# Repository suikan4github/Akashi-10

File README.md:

# Akashi-10
Test board of the EL-210 calculator
## Description
This board is developed to test the functionality of the EL-210 Calculator controller. The [EL-210](https://vintage-technology.club/pages/calculators/sharp/sharpel210.htm) was released from SHARP Corporation at 1980. 

This board tests its internal 9 digits VFD and 9x3 matrix keyboard. All signals and power from internal AA*2 batteries are taken out by 40pin headers. 
## Pin assignment
The ping assignment of the 40pin headers are as followings : 

 Pin | Symbol | Pin | Symbol 
 ----|--------|-----|-------
 1   | H1     | 2   | H2
 3   | a      | 4   | 
 5   | D8     | 6   | KR0
 7   | g      | 8   | KR1
 9   | D7     | 10  | KR2
 11  | f      | 12  | KC0
 13  | D6     | 14  | KC1
 15  | e      | 16  | KC2
 17  | D5     | 18  | KC3
 19  | D4     | 20  | KC4
 21  | d      | 22  | KC5
 23  | D3     | 24  | KC6
 25  | dp     | 26  | KC7
 27  | D2     | 28  | KC8
 29  | c      | 20  | 
 31  | D1     | 32  | 
 33  | b      | 34  | 
 35  | D0     | 36  | 
 37  | H2     | 38  | 
 39  | H1     | 20  | 

Where odd and even pins are signals of the VFD and the key matrix. 
- H1, H2 : Heater.
- a .. f and dp : Segments ( Anode ).
- D0 .. D8 : Digits ( grid ). 
- R1 .. R3 : Row 1 .. 3 of the key matrix.
- C0 .. C8 : Column 0 .. 8 of the key matrix.

## Gallery
This is photo of the version 1.0.2.

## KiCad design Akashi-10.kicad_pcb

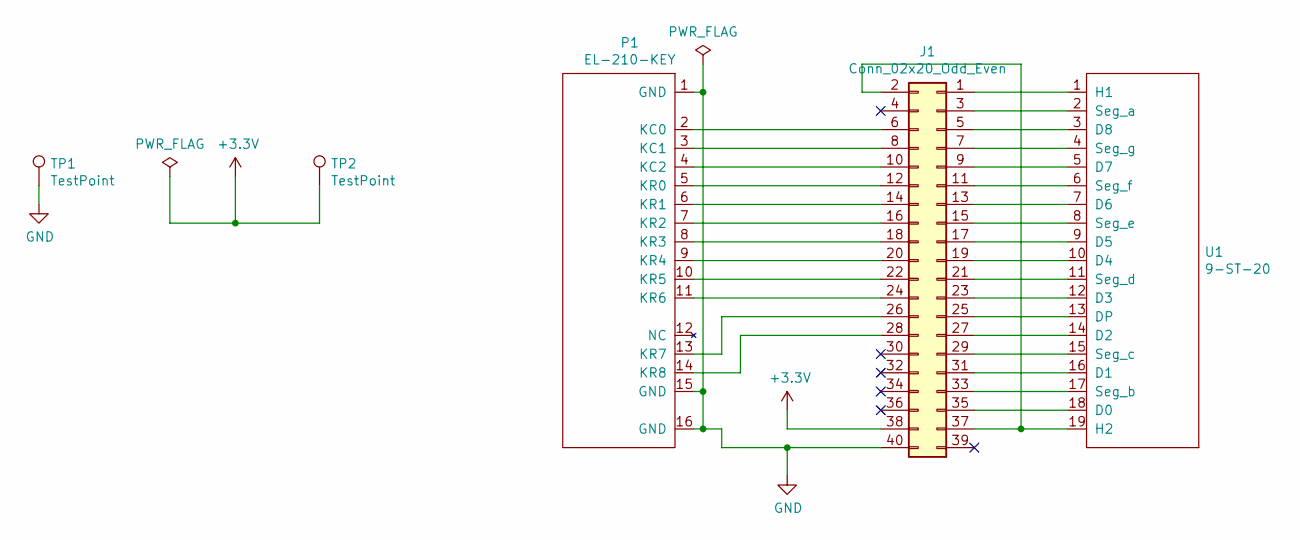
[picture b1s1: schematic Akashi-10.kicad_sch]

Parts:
J1: Conn_02x20_Odd_Even; PinHeader_2x20_P2.54mm_Vertical
P1: EL-210-KEY
TP1, TP2: TestPoint; TestPoint_Loop_D2.60mm_Drill0.9mm_Beaded
U1: 9-ST-20

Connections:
+3V3: J1.38, TP2.1
GND: J1.40, P1.1 (GND), P1.15 (GND), P1.16 (GND), TP1.1
unnamed: J1.1, U1.1 (H1)
unnamed: J1.2, J1.37, U1.19 (H2)
unnamed: J1.3, U1.2 (Seg_a)
unnamed: J1.5, U1.3 (D8)
unnamed: J1.6, P1.2 (KC0)
unnamed: J1.7, U1.4 (Seg_g)
unnamed: J1.8, P1.3 (KC1)
unnamed: J1.9, U1.5 (D7)
unnamed: J1.10, P1.4 (KC2)
unnamed: J1.11, U1.6 (Seg_f)
unnamed: J1.12, P1.5 (KR0)
unnamed: J1.13, U1.7 (D6)
unnamed: J1.14, P1.6 (KR1)
unnamed: J1.15, U1.8 (Seg_e)
unnamed: J1.16, P1.7 (KR2)
unnamed: J1.17, U1.9 (D5)
unnamed: J1.18, P1.8 (KR3)
unnamed: J1.19, U1.10 (D4)
unnamed: J1.20, P1.9 (KR4)
unnamed: J1.21, U1.11 (Seg_d)
unnamed: J1.22, P1.10 (KR5)
unnamed: J1.23, U1.12 (D3)
unnamed: J1.24, P1.11 (KR6)
unnamed: J1.25, U1.13 (DP)
unnamed: J1.26, P1.13 (KR7)
unnamed: J1.27, U1.14 (D2)
unnamed: J1.28, P1.14 (KR8)
unnamed: J1.29, U1.15 (Seg_c)
unnamed: J1.31, U1.16 (D1)
unnamed: J1.33, U1.17 (Seg_b)
unnamed: J1.35, U1.18 (D0)

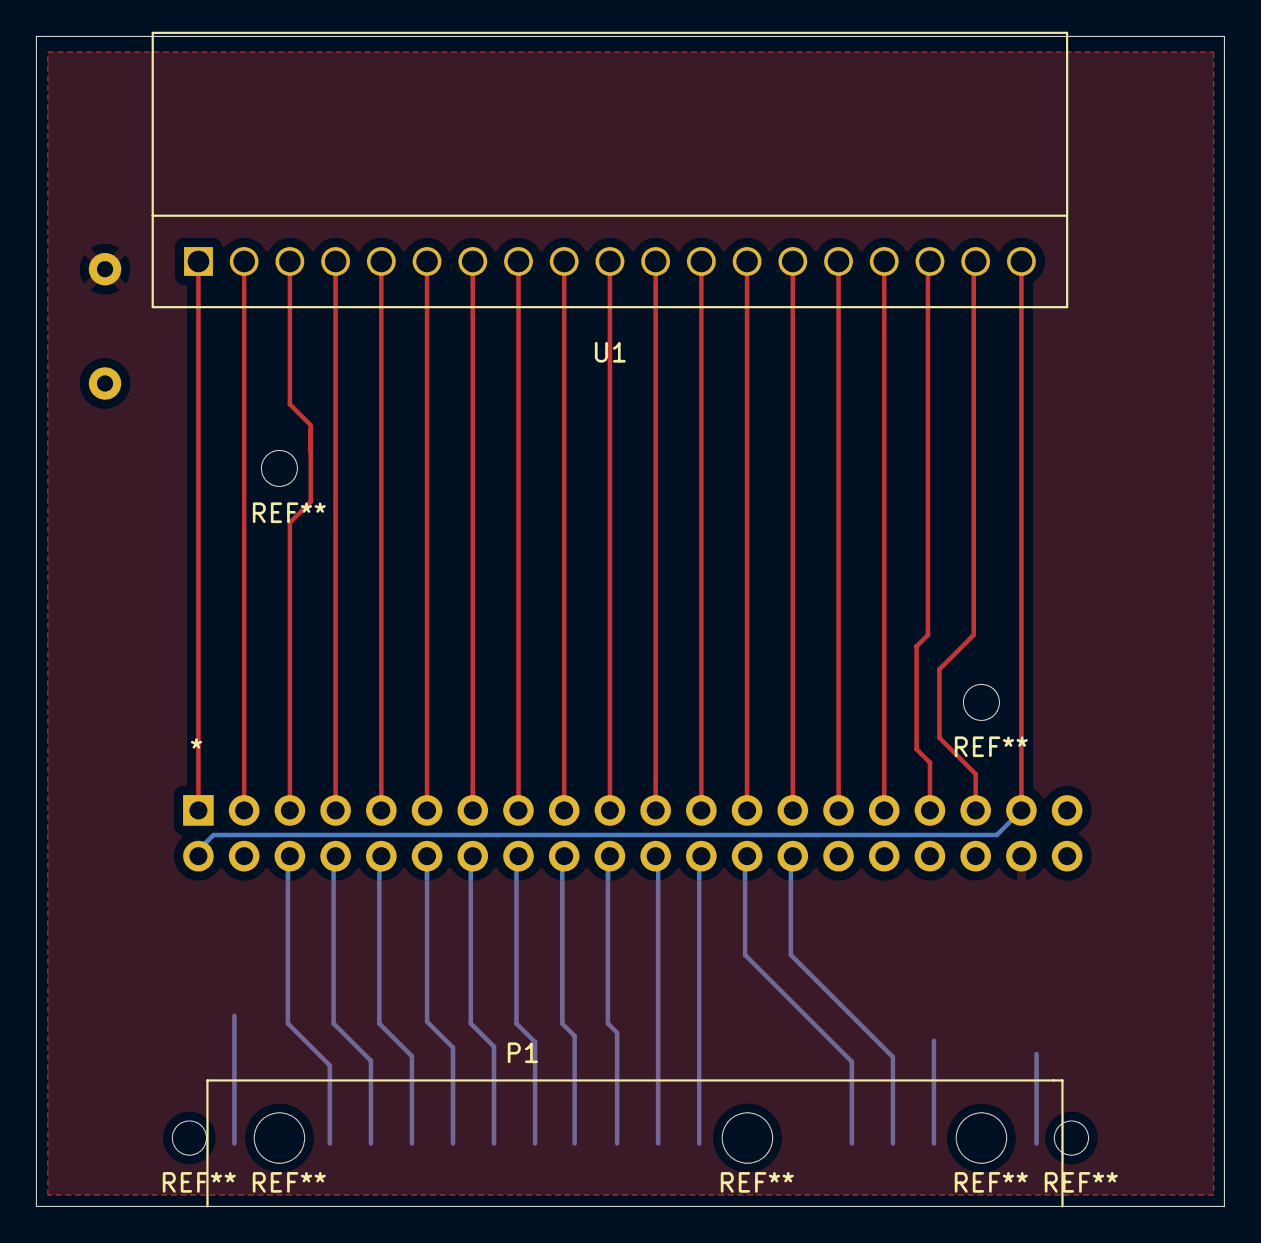
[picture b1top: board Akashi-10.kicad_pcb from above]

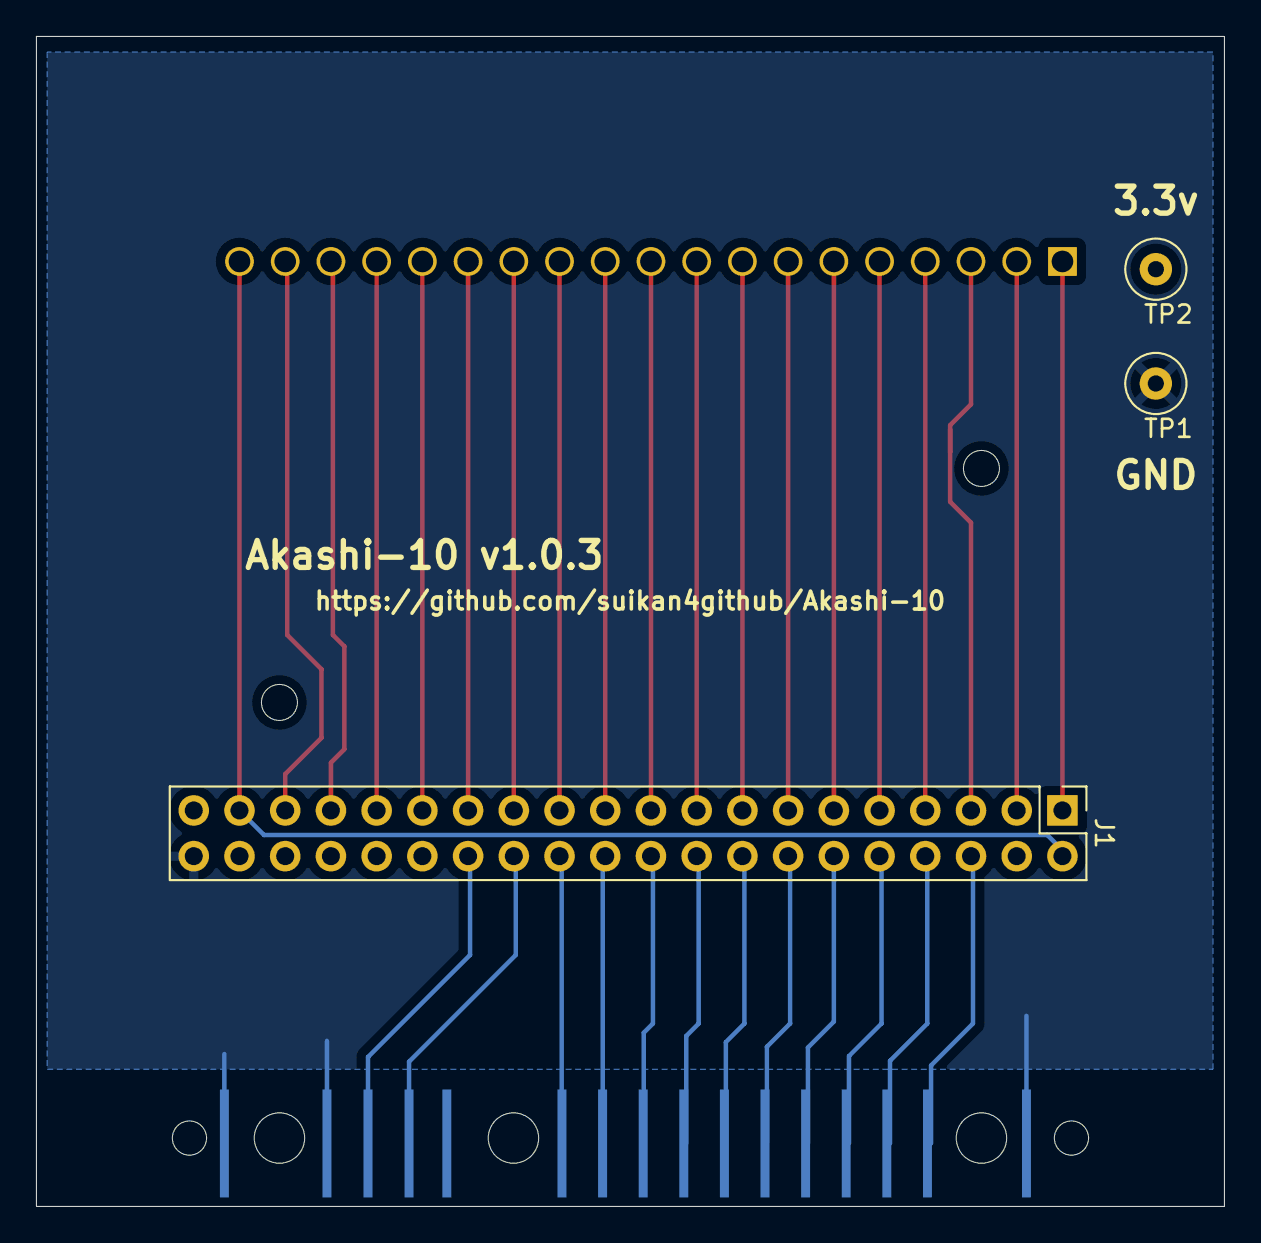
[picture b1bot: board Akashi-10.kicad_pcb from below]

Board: 2 copper layers, 66.0 x 65.0 mm, 5 parts (3 on the bottom side), 33 nets.

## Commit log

2022-06-04 Add 9-ST-20 symbol and footprint
2022-06-05 Add EL-210-key
2022-06-09 place initial layout
2022-06-12 Add holes
2022-06-12 All routed
    No DRC error
2022-06-12 Add version number to Silk
2022-06-12 Sent v1.0.0 to FusionPCB
2022-06-25 P1 pattern fixed.
    Hole size changed. GND/3.3V position changed.
2022-07-10 Add lost holes.
2022-07-11 Lock hole footprints on PCB.
    To prevent delete them during the updating PCB from schematics.
2022-08-11 Apply library modification to board.
2022-10-11 v1.0.2
2023-01-11 Fixed name of the KEY matrix sisgnal.
    The Row signal order was up-side-down. Fixed.
    The Col signal was 1 origin. Fixed as 0 origin.
    Sylscreen modfified.
2023-01-11 Add pin 1 mark to the connector.
    Add pin 1 mark to the connector of the layout.
    Movied Testpoint ( 3.3 and GND hole )
    Update photo.
